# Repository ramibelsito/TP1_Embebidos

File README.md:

# TP1_Embebidos
Control de Acceso Mediante Tarjeta Magnética

## ToDoList
 
 1. Hacer la lógica para leer y procesar los datos de la tarjeta
 2. Terminar el driver del Display
 3. Organizar manejo de usuarios
 4. Hacer FSM General
 5. Terminar App

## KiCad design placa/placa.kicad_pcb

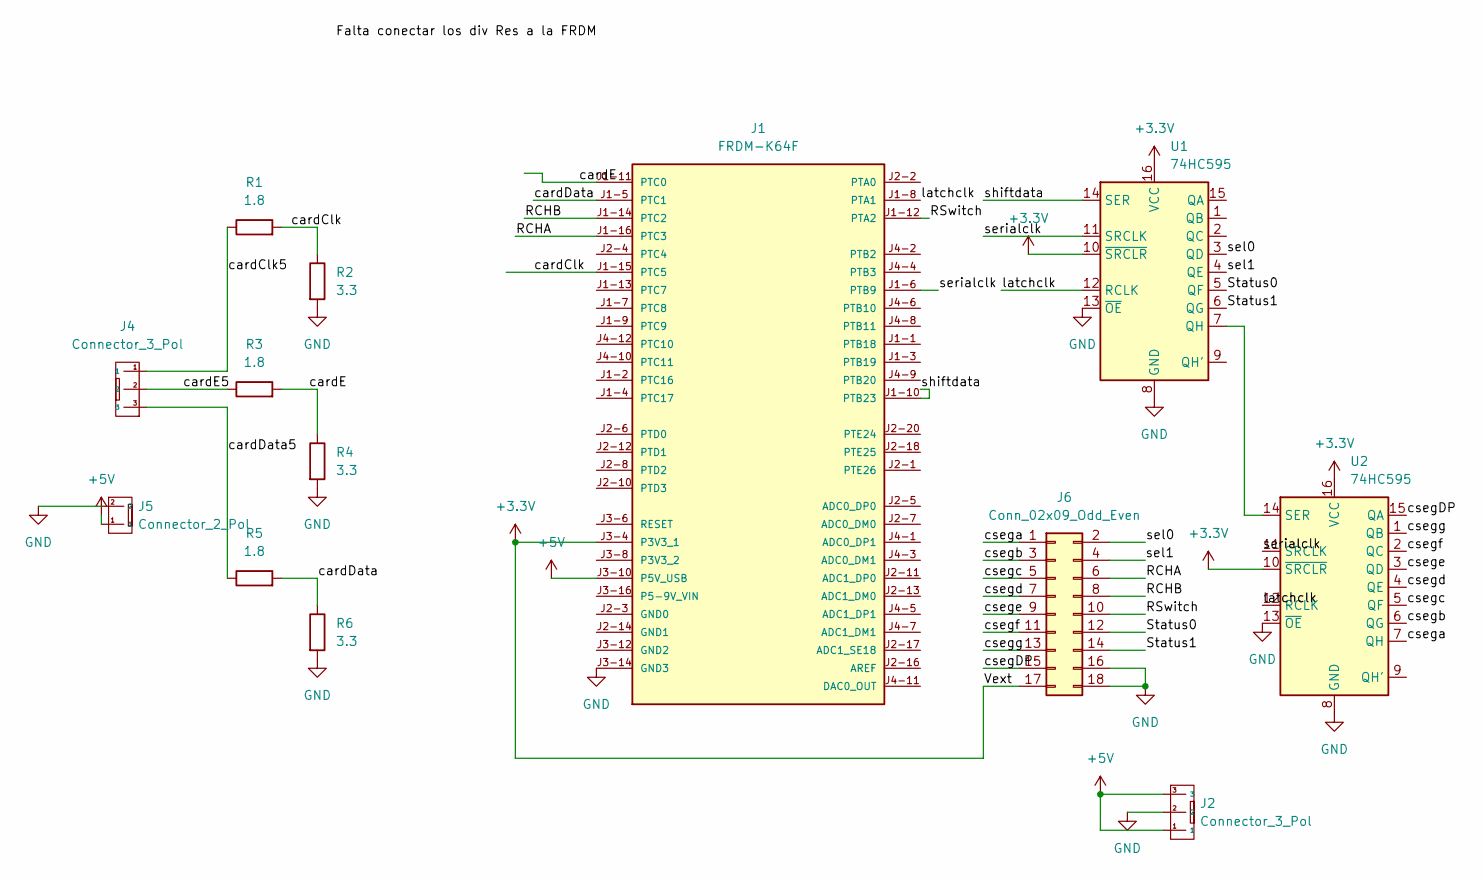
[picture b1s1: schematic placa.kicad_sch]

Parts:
J1: FRDM-K64F
J2, J4: Connector_3_Pol; Molex_1x03_P2.54mm
J5: Connector_2_Pol; Molex_1x02_P2.54mm
J6: Conn_02x09_Odd_Even; PinHeader_2x09_P2.54mm_Vertical
R1, R3, R5: 1.8; R_0.25W
R2, R4, R6: 3.3; R_0.25W
U1, U2: 74HC595; DIP-16_W7.62mm_LongPads

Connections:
+3.3V: J1.J3-4 (P3V3_1), J6.17, U1.10 (~SRCLR), U1.16 (VCC), U2.10 (~SRCLR), U2.16 (VCC)
+5V: J1.J3-10 (P5V_USB), J2.1, J2.3, J5.1
/RCHA: J1.J1-16 (PTC3), J6.6
/RCHB: J1.J1-14 (PTC2), J6.8
/RSwitch: J1.J1-12 (PTA2), J6.10
/Status0: J6.12, U1.5 (QF)
/Status1: J6.14, U1.6 (QG)
/cardClk: J1.J1-15 (PTC5), R1.2, R2.1
/cardClk5: J4.1, R1.1
/cardData: J1.J1-5 (PTC1), R5.2, R6.1
/cardData5: J4.3, R5.1
/cardE: J1.J1-11 (PTC0), R3.2, R4.1
/cardE5: J4.2, R3.1
/csegDP: J6.15, U2.15 (QA)
/csega: J6.1, U2.7 (QH)
/csegb: J6.3, U2.6 (QG)
/csegc: J6.5, U2.5 (QF)
/csegd: J6.7, U2.4 (QE)
/csege: J6.9, U2.3 (QD)
/csegf: J6.11, U2.2 (QC)
/csegg: J6.13, U2.1 (QB)
/latchclk: J1.J1-8 (PTA1), U1.12 (RCLK), U2.12 (RCLK)
/sel0: J6.2, U1.3 (QD)
/sel1: J6.4, U1.4 (QE)
/serialclk: J1.J1-6 (PTB9), U1.11 (SRCLK), U2.11 (SRCLK)
/shiftdata: J1.J1-10 (PTB23), U1.14 (SER)
GND: J1.J3-14 (GND3), J2.2, J5.2, J6.16, J6.18, R2.2, R4.2, R6.2, U1.8 (GND), U1.13 (~OE), U2.8 (GND), U2.13 (~OE)
unnamed: U1.7 (QH), U2.14 (SER)

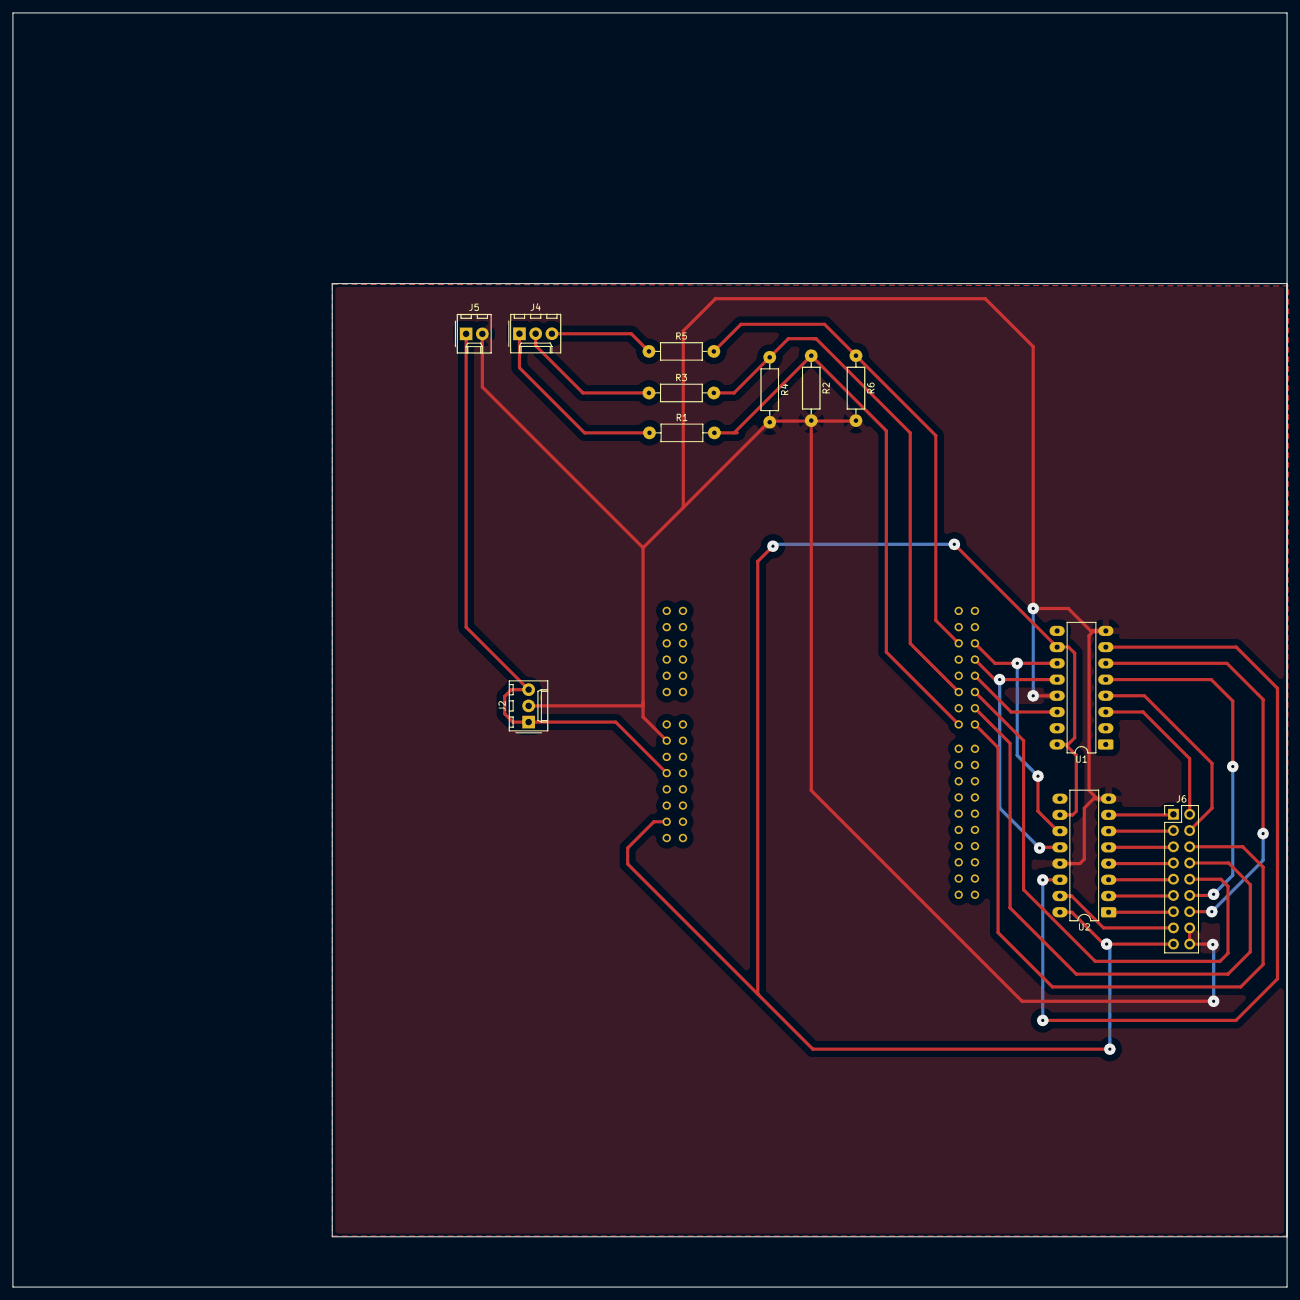
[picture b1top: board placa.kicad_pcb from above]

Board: 2 copper layers, 199.5 x 199.5 mm, 13 parts (1 on the bottom side), 28 nets.

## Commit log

2026-04-01 Actualización proyecto base - Guía 2
2026-04-01 Algunos Cambios
2026-04-01 Organización
2026-04-01 Todo list y organización de archivos
2026-04-02 pisr logic for various periodic interruptions
2026-04-03 Arbol de funciones target armado
2026-04-04 Avance en encoder wheel.c
2026-04-06 Encoder casi funcando
2026-04-07 shiftreg
2026-04-08 No se porque se habia modificado el wheel.c
2026-04-09 chore(shift): fix errors and refactor to use uin16_t instead of bool[16]
2026-04-09 feat: initial hal display impl
2026-04-09 agregue una capa de leds y el encoder funciona joya
2026-04-09 agregue leds y el encoder funciona joya
2026-04-09 Se esta cumpliendo el interrupt de la tarjeta, falta logica
2026-04-10 Falta testear la logica
2026-04-10 Agrego la consigna
2026-04-10 adelanto card.c casero
2026-04-11 Procesamiento de la data de la tarjeta. Falta testear
2026-04-11 feat: finish display impl
2026-04-11 chore: use enum return type for readWheel
2026-04-11 Comentarios en card.c
2026-04-11 Procesamiento del lector de tarjetas testeado
2026-04-11 reescribi los pines tal como la placa al board.h
2026-04-12 casi funciona tarjeta. Falla a la tercera lectura
2026-04-12 feat(app): id input
2026-04-12 feat(app): display intensity
2026-04-12 pulleando pero me obliga a committear
2026-04-13 Funciona joya display
2026-04-13 chore: make internal display functions static
2026-04-13 chore: small id input refactor
2026-04-13 fix: id input cursor
2026-04-13 feat: password input
2026-04-13 fix: only allow confirming password of 4 or 5 characters
2026-04-13 integracion andando, falta pulir interfaz
2026-04-13 chore: enable dot for debugging
2026-04-13 fix(display): blink logic
2026-04-13 quality of life improvements
2026-04-13 Funciona correctamente el ingreso de id por tarjeta
2026-04-13 chore: add dot to select digit state in inputs
2026-04-13 chore: ass pre-existing users
2026-04-13 feat: display led handling
2026-04-13 chore: formatting
2026-04-13 fix: variable declaration inside case without braces
2026-04-13 userConfiged
2026-04-13 agregue users y cosas
2026-04-13 mini cambio a app
2026-04-13 feat: timers
2026-04-13 fix: timers
2026-04-13 Condicion necesaria, y "suficiente"
2026-04-13 Tasa de refresco display mas rapida, sino parpadeaba y no cambiaba la intensidad bien
2026-04-13 Manual de referencia
2026-04-13 cambios last min
2026-04-13 chore: rever shift masks
2026-04-13 feat: pass change + more timers
2026-04-13 usuario agregado, sube
2026-04-13 maybe fix error messages
2026-04-14 Comit final Codigo.
2026-04-14 Manual de usuario
